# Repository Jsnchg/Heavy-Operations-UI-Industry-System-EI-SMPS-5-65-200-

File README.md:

# Heavy-Operations-UI-Industry-System-EI-SMPS-5-65-200-

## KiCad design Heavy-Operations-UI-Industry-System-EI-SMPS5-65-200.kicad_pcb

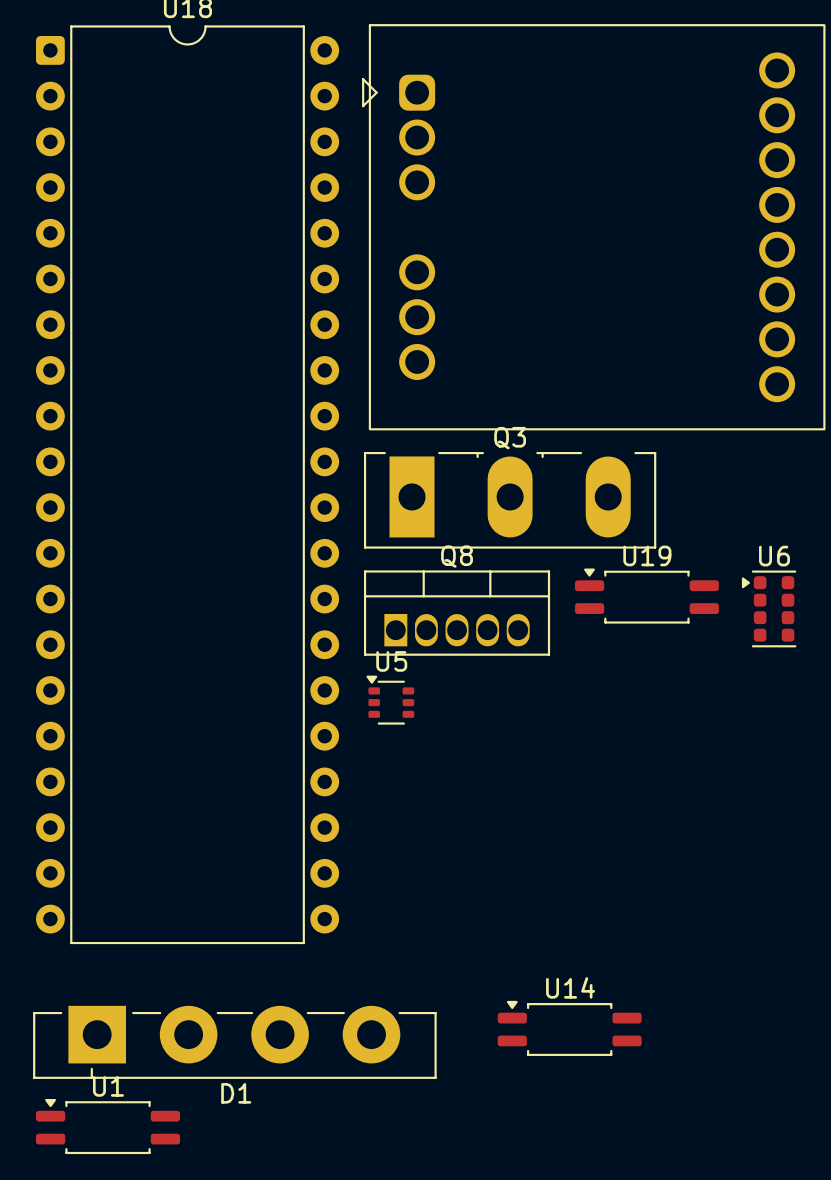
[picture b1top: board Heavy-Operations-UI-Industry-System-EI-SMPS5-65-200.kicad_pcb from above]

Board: 2 copper layers, 10 parts (0 on the bottom side), 9 nets, no tracks yet.

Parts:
D1: GBU4M; Diode_Bridge_Vishay_GBU
Q3: C2M0025120D; TO-247-3_Vertical
Q8: IPS6011PBF; TO-220-5_Vertical
TR1: Wuerth_760871131; Transformer_Wuerth_760871131
U1, U19: FODM217C; SOP-4_4.4x2.6mm_P1.27mm
U5: NCS210; SOT-363_SC-70-6
U6: RPR-0521RS; Rohm_RPR-0521RS
U14: FODM217D; SOP-4_4.4x2.6mm_P1.27mm
U18: 8080; DIP-40_W15.24mm

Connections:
AC: D1.4 (-), Q3.2 (D)
unnamed: D1.1 (+), U1.1
unnamed: TR1.9, TR1.10
unnamed: TR1.13, TR1.14
unnamed: U5.2 (GND), U6.2 (SCL)
unnamed: TR1.7, TR1.8, U18.11 (-5V)
unnamed: TR1.3, U18.2 (GND)
unnamed: TR1.1, U18.14 (INT)
unnamed: TR1.11, TR1.12, U18.19 (SYNC)

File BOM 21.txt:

Heavy-Operations-UI-Industry-System-EI-SMPS5-65-200
BOM 21

A. Switched-Mode Power Supply
1. AC

B. SMPS (5 - 65W)
1. AC
2. NCP51530
3. NCP1568D
4. GBU4M
5. NMOS X3
6. NCP1654
7. NCP4305
8. FODM217D
9. NCP731
10. NCV6324

C. SMPS (65 - 200W)
1. AC
2. GBU4M
3. FODM217C
4. NMOS
5. D_Capacitance
6. NCP431

D. SMPS (>200W)
1. AC
2. D_Schottky_Filled
3. NJFET x2
4. NCP51530
5. NCP4390
6. NCS210R
7. C2M0025120D
8. NCP1681
9. NCP4305
10. NCD9830
11. Wuerth_760871131
12. NCV6324
13. NIS3071
14. NCP731


Total:
1. AC x3
2. D_Schottky_Filled 
3. NJFET x2
4. NCP51530 x2
5. NCP4390
6. NCS210R
7. C2M0025120D
8. NCP1681
9. NCP4305
10. NCD9830
11. Wuerth_760871131
12. NCV6324
13. NIS3071 
14. NCP731 x2
15. NMOS x3
16. GBU4M x2
17. FODM217C
18. NCP431
19. D_Capacitance

Note: 
Component 19 is added to make the project more unique
